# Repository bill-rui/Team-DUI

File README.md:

# Team-DUI
When breathalyzer meets RC car.

All code used are in code folder.
All eagle related files are in eagle folder.

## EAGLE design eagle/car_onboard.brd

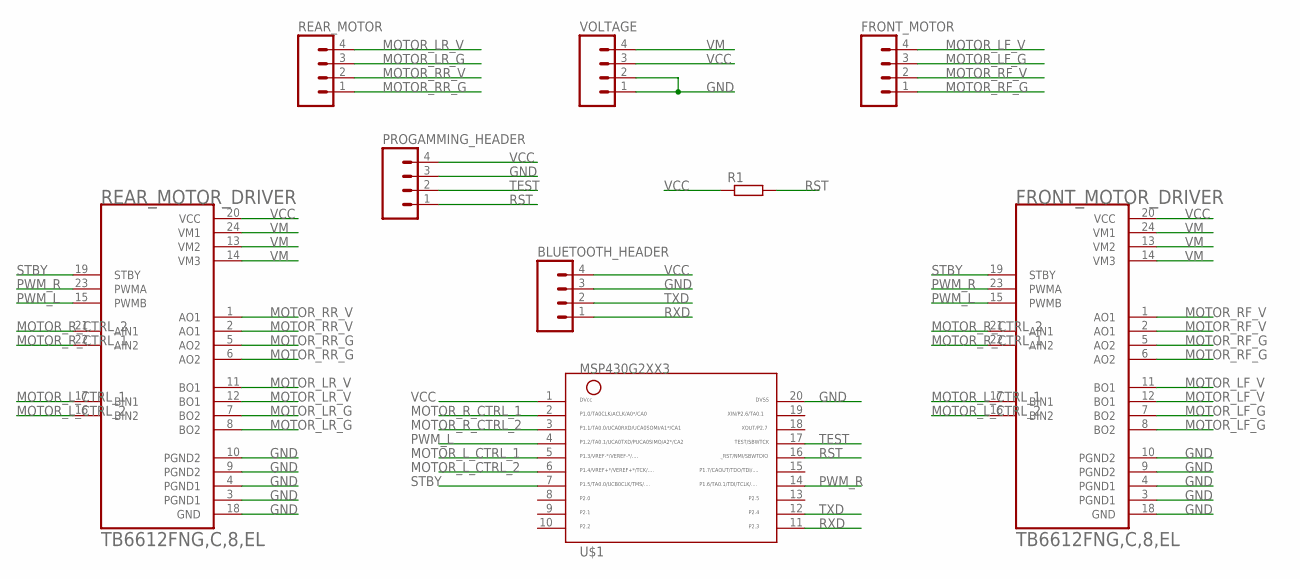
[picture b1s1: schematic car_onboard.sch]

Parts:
BLUETOOTH_HEADER: HEADER_1X04LOCK; 1X04_LOCK
FRONT_MOTOR: HEADER_1X04LOCK; 1X04_LOCK
FRONT_MOTOR_DRIVER: TB6612FNG,C,8,EL; SOP65P760X160-24N
PROGAMMING_HEADER: HEADER_1X04LOCK; 1X04_LOCK
R1: R-EU_R1206; R1206
REAR_MOTOR: HEADER_1X04LOCK; 1X04_LOCK
REAR_MOTOR_DRIVER: TB6612FNG,C,8,EL; SOP65P760X160-24N
U$1: MSP430G2XX3TSSOP; PW20
VOLTAGE: HEADER_1X04LOCK; 1X04_LOCK

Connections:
GND: BLUETOOTH_HEADER.3, FRONT_MOTOR_DRIVER.3 (PGND1), FRONT_MOTOR_DRIVER.4 (PGND1), FRONT_MOTOR_DRIVER.9 (PGND2), FRONT_MOTOR_DRIVER.10 (PGND2), FRONT_MOTOR_DRIVER.18 (GND), PROGAMMING_HEADER.3, REAR_MOTOR_DRIVER.3 (PGND1), REAR_MOTOR_DRIVER.4 (PGND1), REAR_MOTOR_DRIVER.9 (PGND2), REAR_MOTOR_DRIVER.10 (PGND2), REAR_MOTOR_DRIVER.18 (GND), U$1.20, VOLTAGE.1, VOLTAGE.2
MOTOR_LF_G: FRONT_MOTOR.3, FRONT_MOTOR_DRIVER.7 (BO2), FRONT_MOTOR_DRIVER.8 (BO2)
MOTOR_LF_V: FRONT_MOTOR.4, FRONT_MOTOR_DRIVER.11 (BO1), FRONT_MOTOR_DRIVER.12 (BO1)
MOTOR_LR_G: REAR_MOTOR.3, REAR_MOTOR_DRIVER.7 (BO2), REAR_MOTOR_DRIVER.8 (BO2)
MOTOR_LR_V: REAR_MOTOR.4, REAR_MOTOR_DRIVER.11 (BO1), REAR_MOTOR_DRIVER.12 (BO1)
MOTOR_L_CTRL_1: FRONT_MOTOR_DRIVER.17 (BIN1), REAR_MOTOR_DRIVER.17 (BIN1), U$1.5
MOTOR_L_CTRL_2: FRONT_MOTOR_DRIVER.16 (BIN2), REAR_MOTOR_DRIVER.16 (BIN2), U$1.6
MOTOR_RF_G: FRONT_MOTOR.1, FRONT_MOTOR_DRIVER.5 (AO2), FRONT_MOTOR_DRIVER.6 (AO2)
MOTOR_RF_V: FRONT_MOTOR.2, FRONT_MOTOR_DRIVER.1 (AO1), FRONT_MOTOR_DRIVER.2 (AO1)
MOTOR_RR_G: REAR_MOTOR.1, REAR_MOTOR_DRIVER.5 (AO2), REAR_MOTOR_DRIVER.6 (AO2)
MOTOR_RR_V: REAR_MOTOR.2, REAR_MOTOR_DRIVER.1 (AO1), REAR_MOTOR_DRIVER.2 (AO1)
MOTOR_R_CTRL_1: FRONT_MOTOR_DRIVER.22 (AIN2), REAR_MOTOR_DRIVER.22 (AIN2), U$1.2
MOTOR_R_CTRL_2: FRONT_MOTOR_DRIVER.21 (AIN1), REAR_MOTOR_DRIVER.21 (AIN1), U$1.3
PWM_L: FRONT_MOTOR_DRIVER.15 (PWMB), REAR_MOTOR_DRIVER.15 (PWMB), U$1.4
PWM_R: FRONT_MOTOR_DRIVER.23 (PWMA), REAR_MOTOR_DRIVER.23 (PWMA), U$1.14
RST: PROGAMMING_HEADER.1, R1.2, U$1.16
RXD: BLUETOOTH_HEADER.1, U$1.11
STBY: FRONT_MOTOR_DRIVER.19 (STBY), REAR_MOTOR_DRIVER.19 (STBY), U$1.7
TEST: PROGAMMING_HEADER.2, U$1.17
TXD: BLUETOOTH_HEADER.2, U$1.12
VCC: BLUETOOTH_HEADER.4, FRONT_MOTOR_DRIVER.20 (VCC), PROGAMMING_HEADER.4, R1.1, REAR_MOTOR_DRIVER.20 (VCC), U$1.1, VOLTAGE.3
VM: FRONT_MOTOR_DRIVER.13 (VM2), FRONT_MOTOR_DRIVER.14 (VM3), FRONT_MOTOR_DRIVER.24 (VM1), REAR_MOTOR_DRIVER.13 (VM2), REAR_MOTOR_DRIVER.14 (VM3), REAR_MOTOR_DRIVER.24 (VM1), VOLTAGE.4

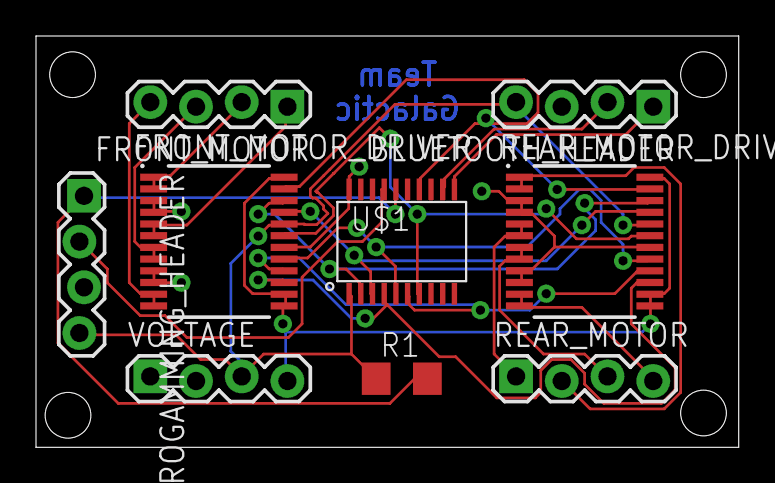
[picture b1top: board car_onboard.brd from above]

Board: 2 copper layers, 39.0 x 22.9 mm, 9 parts (0 on the bottom side), 22 nets.

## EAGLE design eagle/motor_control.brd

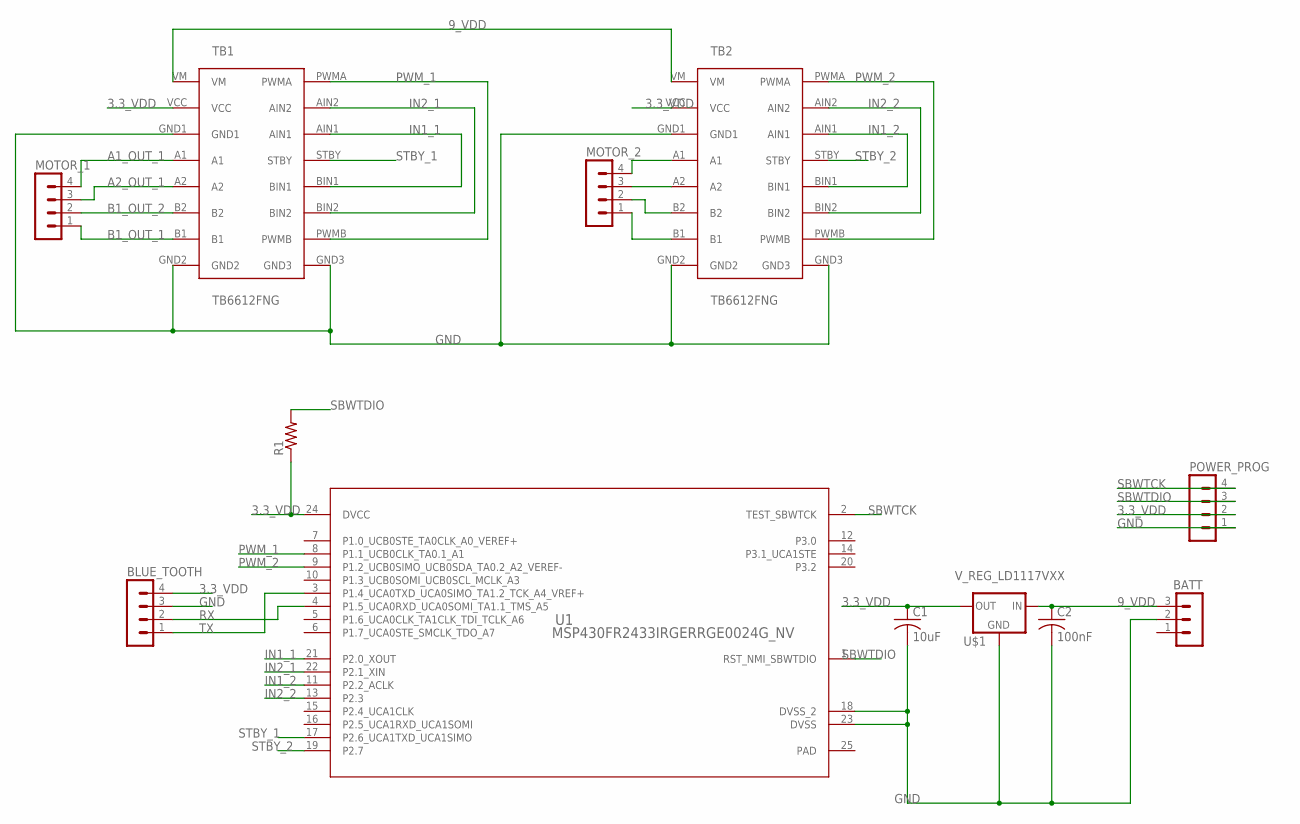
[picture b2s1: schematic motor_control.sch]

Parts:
BATT: MA03-1
BLUE_TOOTH: MA04-1
C1: 10uF; C1206
C2: 100nF; C1206
MOTOR_1, MOTOR_2: MA04-1
POWER_PROG: MA04-1
R1: R-US_R1206; R1206
TB1, TB2: TB6612FNG
U1: MSP430FR2433IRGERRGE0024G_NV; RGE0024G_NV
U$1: V_REG_LD1117VXX; 78XXL

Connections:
3.3_VDD: BLUE_TOOTH.4, C1.1, POWER_PROG.2, R1.1, TB1.VCC, TB2.VCC, U1.24 (DVCC), U$1.GND (OUT)
9_VDD: BATT.3, C2.1, TB1.VM, TB2.VM, U$1.OUT (IN)
A1_OUT_1: MOTOR_1.4, TB1.A1
A2_OUT_1: MOTOR_1.3, TB1.A2
B1_OUT_1: MOTOR_1.1, TB1.B1
B1_OUT_2: MOTOR_1.2, TB1.B2
GND: BATT.2, BLUE_TOOTH.3, C1.2, C2.2, POWER_PROG.1, TB1.GND1, TB1.GND2, TB1.GND3, TB2.GND1, TB2.GND2, TB2.GND3, U1.18 (DVSS_2), U1.23 (DVSS), U$1.IN (GND)
IN1_1: TB1.AIN1, TB1.BIN1, U1.21 (P2.0_XOUT)
IN1_2: TB2.AIN1, TB2.BIN1, U1.11 (P2.2_ACLK)
IN2_1: TB1.AIN2, TB1.BIN2, U1.22 (P2.1_XIN)
IN2_2: TB2.AIN2, TB2.BIN2, U1.13 (P2.3)
unnamed: MOTOR_2.4, TB2.A1
unnamed: MOTOR_2.3, TB2.A2
unnamed: MOTOR_2.2, TB2.B2
unnamed: MOTOR_2.1, TB2.B1
PAD: U1.25 (PAD)
PWM_1: TB1.PWMA, TB1.PWMB, U1.8 (P1.1_UCB0CLK_TA0.1_A1)
PWM_2: TB2.PWMA, TB2.PWMB, U1.9 (P1.2_UCB0SIMO_UCB0SDA_TA0.2_A2_VEREF-)
RX: BLUE_TOOTH.2, U1.4 (P1.5_UCA0RXD_UCA0SOMI_TA1.1_TMS_A5)
SBWTCK: POWER_PROG.4, U1.2 (TEST_SBWTCK)
SBWTDIO: POWER_PROG.3, R1.2, U1.1 (RST_NMI_SBWTDIO)
STBY_1: TB1.STBY, U1.17 (P2.6_UCA1TXD_UCA1SIMO)
STBY_2: TB2.STBY, U1.19 (P2.7)
TX: BLUE_TOOTH.1, U1.3 (P1.4_UCA0TXD_UCA0SIMO_TA1.2_TCK_A4_VREF+)

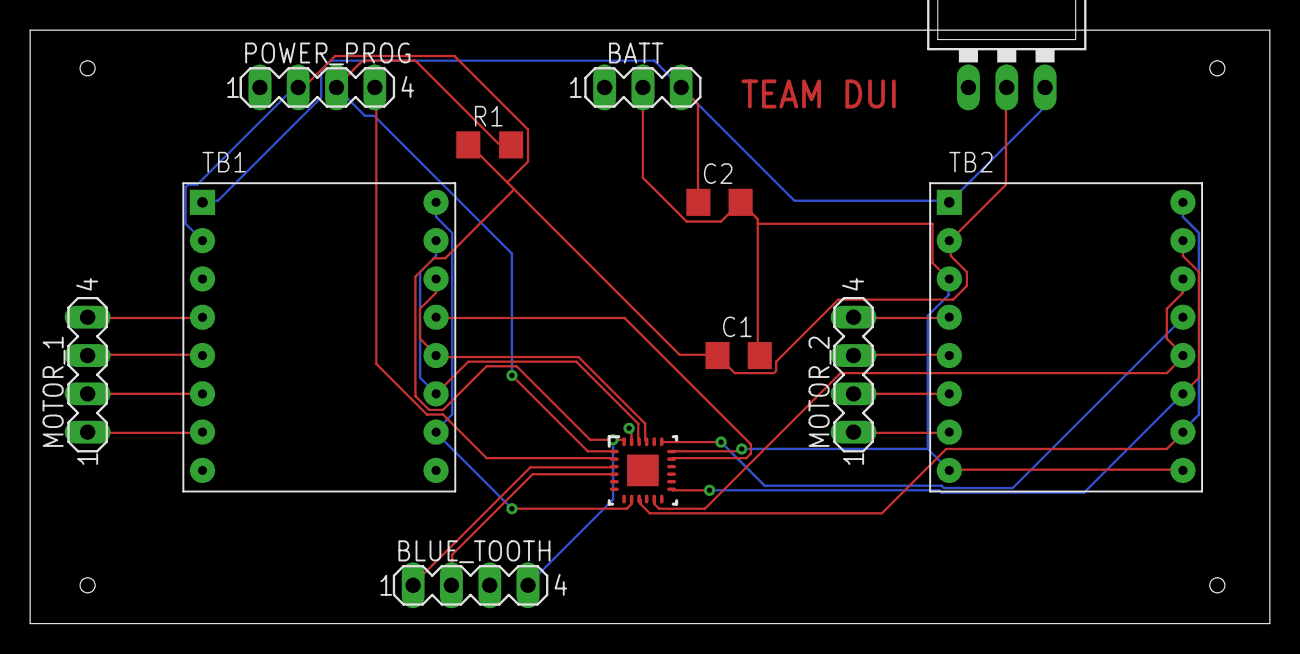
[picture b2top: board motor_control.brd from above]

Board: 2 copper layers, 82.2 x 39.4 mm, 12 parts (0 on the bottom side), 23 nets.

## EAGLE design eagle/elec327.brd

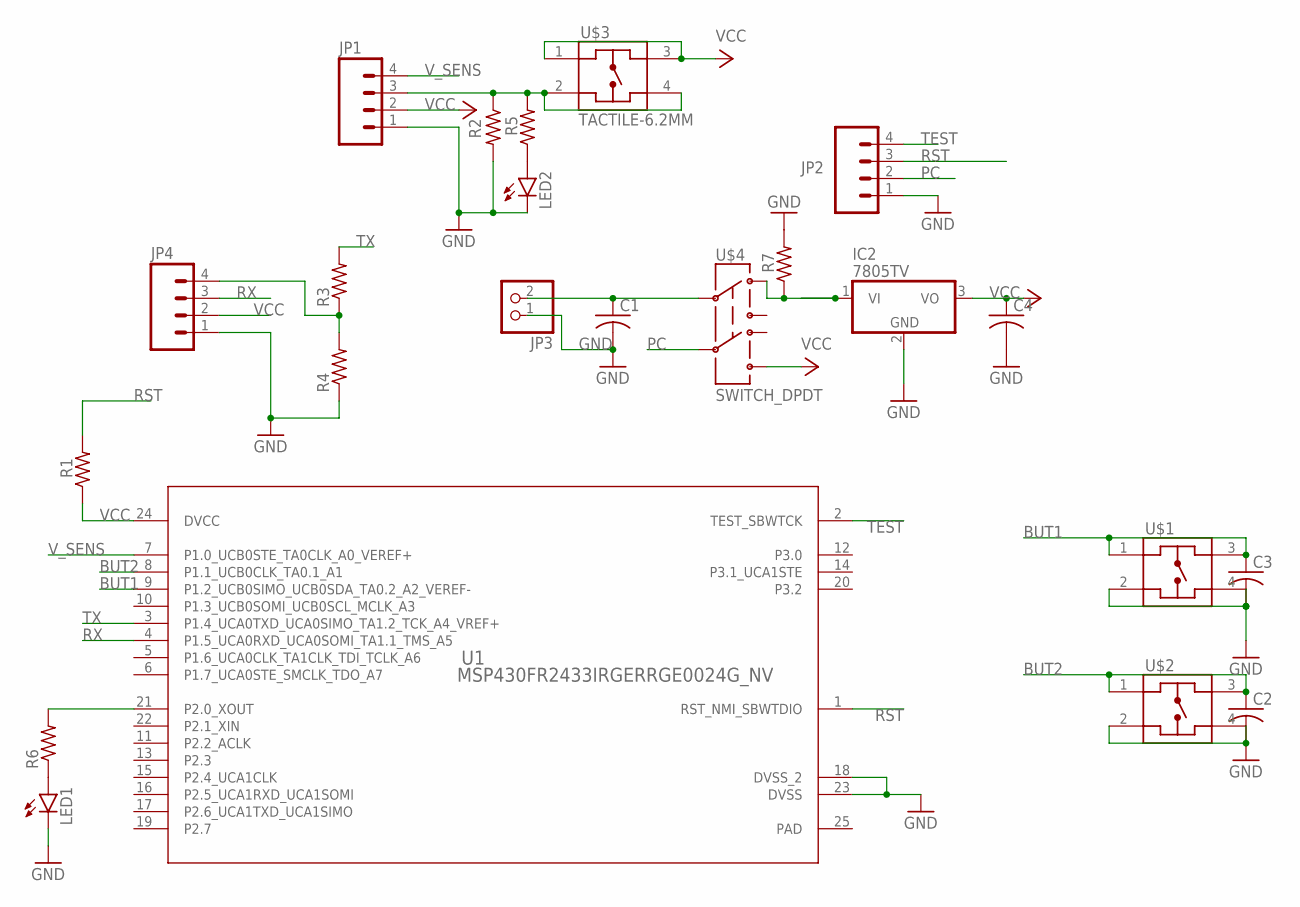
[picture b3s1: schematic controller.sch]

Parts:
C1, C4: C-USC1206; C1206
C2, C3: C-USC0603; C0603
IC2: 7805TV; TO220V
JP1, JP2, JP4: HEADER_1X04LOCK; 1X04_LOCK
JP3: PINHD-1X2; 1X02
LED1, LED2: LED5MM
R1, R2, R3, R4, R5, R6, R7: R-US_R1206; R1206
U1: MSP430FR2433IRGERRGE0024G_NV; RGE0024G_NV
U$1, U$2, U$3: TACTILE-6.2MM; 222_AM
U$4: SWITCH_DPDT; JS_DPDT_TH

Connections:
BUT1: C3.1, U1.9 (P1.2_UCB0SIMO_UCB0SDA_TA0.2_A2_VEREF-), U$1.1, U$1.3
BUT2: C2.1, U1.8 (P1.1_UCB0CLK_TA0.1_A1), U$2.1, U$2.3
GND: C1.2, C2.2, C3.2, C4.2, IC2.2 (GND), JP1.1, JP2.1, JP3.1, JP4.1, LED1.K (C), LED2.K (C), R2.2, R4.1, R7.2, U1.18 (DVSS_2), U1.23 (DVSS), U$1.2, U$1.4, U$2.2, U$2.4
unnamed: IC2.1 (VI), R7.1, U$4.1
unnamed: R6.2, U1.21 (P2.0_XOUT)
unnamed: C1.1, JP3.2, U$4.2
unnamed: JP1.3, R2.1, R5.2, U$3.2, U$3.4
unnamed: LED1.A, R6.1
unnamed: JP4.4, R3.1, R4.2
unnamed: LED2.A, R5.1
PAD: U1.25 (PAD)
PC: JP2.2, U$4.5
RST: JP2.3, R1.2, U1.1 (RST_NMI_SBWTDIO)
RX: JP4.3, U1.4 (P1.5_UCA0RXD_UCA0SOMI_TA1.1_TMS_A5)
TEST: JP2.4, U1.2 (TEST_SBWTCK)
TX: R3.2, U1.3 (P1.4_UCA0TXD_UCA0SIMO_TA1.2_TCK_A4_VREF+)
VCC: C4.1, IC2.3 (VO), JP1.2, JP4.2, R1.1, U1.24 (DVCC), U$3.1, U$3.3, U$4.6
V_SENS: JP1.4, U1.7 (P1.0_UCB0STE_TA0CLK_A0_VEREF+)

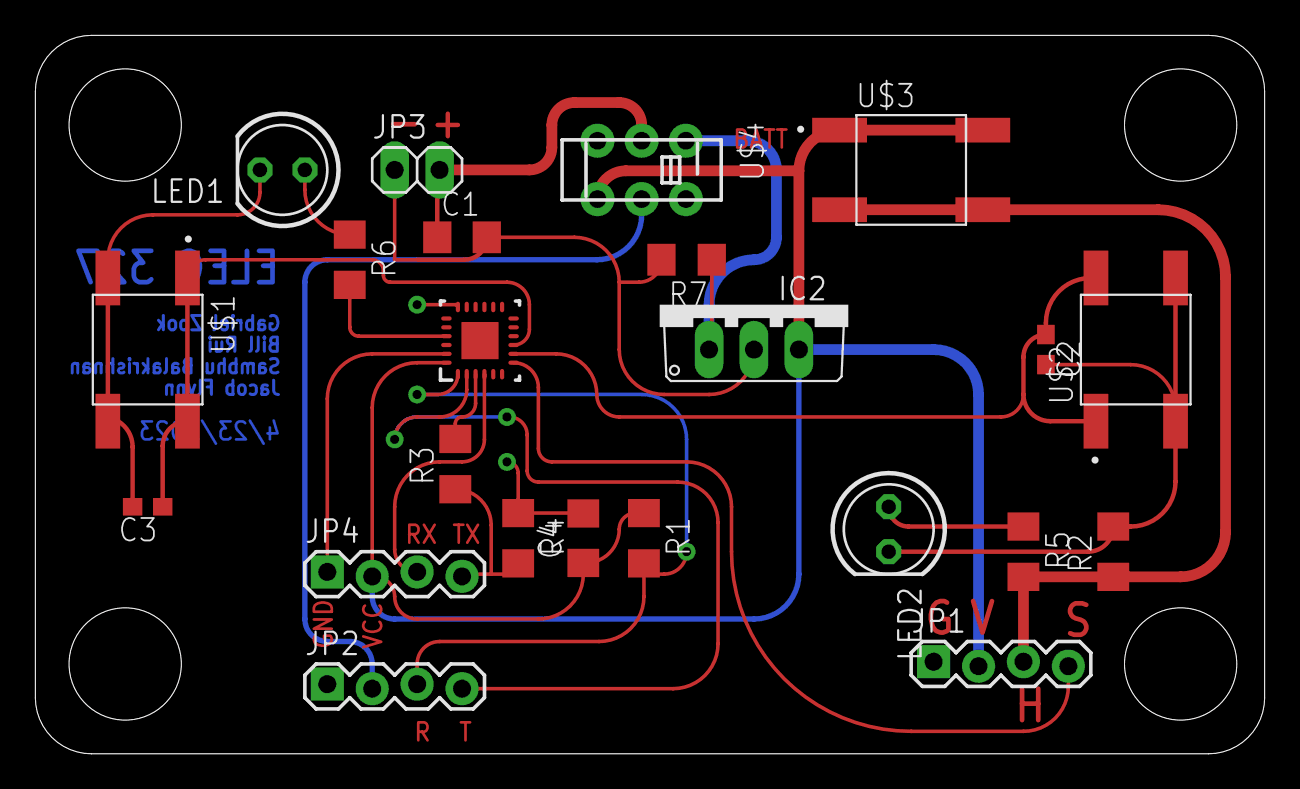
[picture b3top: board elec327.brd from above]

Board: 2 copper layers, 69.5 x 40.6 mm, 23 parts (0 on the bottom side), 17 nets.

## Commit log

2023-05-03 Rename main.c to controller.c
2023-05-03 folders
2023-05-03 motor boards
2023-05-03 V1 of the motor PCB
2023-05-03 Rename elec327.brd to controller.brd
2023-05-03 Rename elec327.sch to controller.sch

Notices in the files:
parts and their libraries:
msp430fr2433: COPYRIGHT: Copyright (C) 2023 Ultra Librarian. All rights reserved.
